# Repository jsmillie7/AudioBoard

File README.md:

# AudioBoard
A repository for a Teensy 4.0 NRF24L01 Audio Transmitter and Receiver board with a built-in codec.

This project supports wireless transmission of mono 16-bit 44.1khz audio bewteen two teensy 4.0 modules.

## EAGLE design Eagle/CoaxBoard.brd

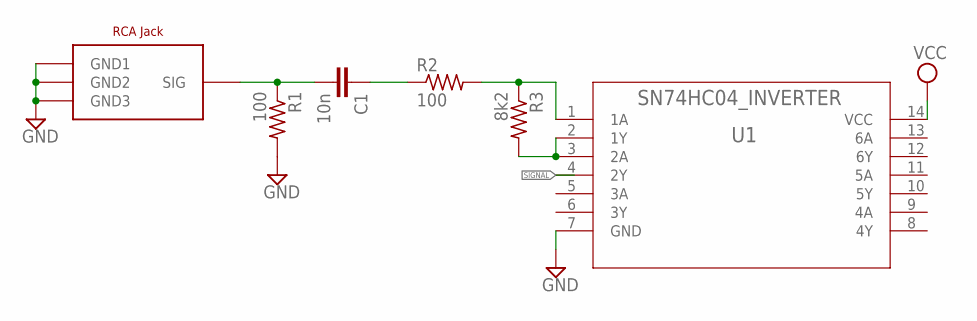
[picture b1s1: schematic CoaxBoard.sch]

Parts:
C1: 10n; C0805
R1, R2: 100; R0805
R3: 8k2; R0805
U1: SN74HC04_INVERTER; NS14
U$1: RCA_JACK

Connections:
GND: R1.2, U1.7 (GND), U$1.GND1, U$1.GND2, U$1.GND3
unnamed: C1.2, R1.1, U$1.SIG
unnamed: C1.1, R2.1
unnamed: R2.2, R3.1, U1.1 (1A)
unnamed: R3.2, U1.2 (1Y), U1.3 (2A)
SIGNAL: U1.4 (2Y)
VCC: U1.14 (VCC)

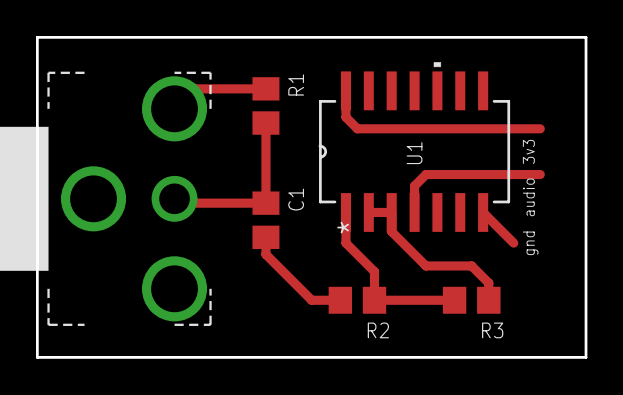
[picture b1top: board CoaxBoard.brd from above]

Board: 2 copper layers, 30.5 x 17.8 mm, 6 parts (0 on the bottom side), 5 nets.

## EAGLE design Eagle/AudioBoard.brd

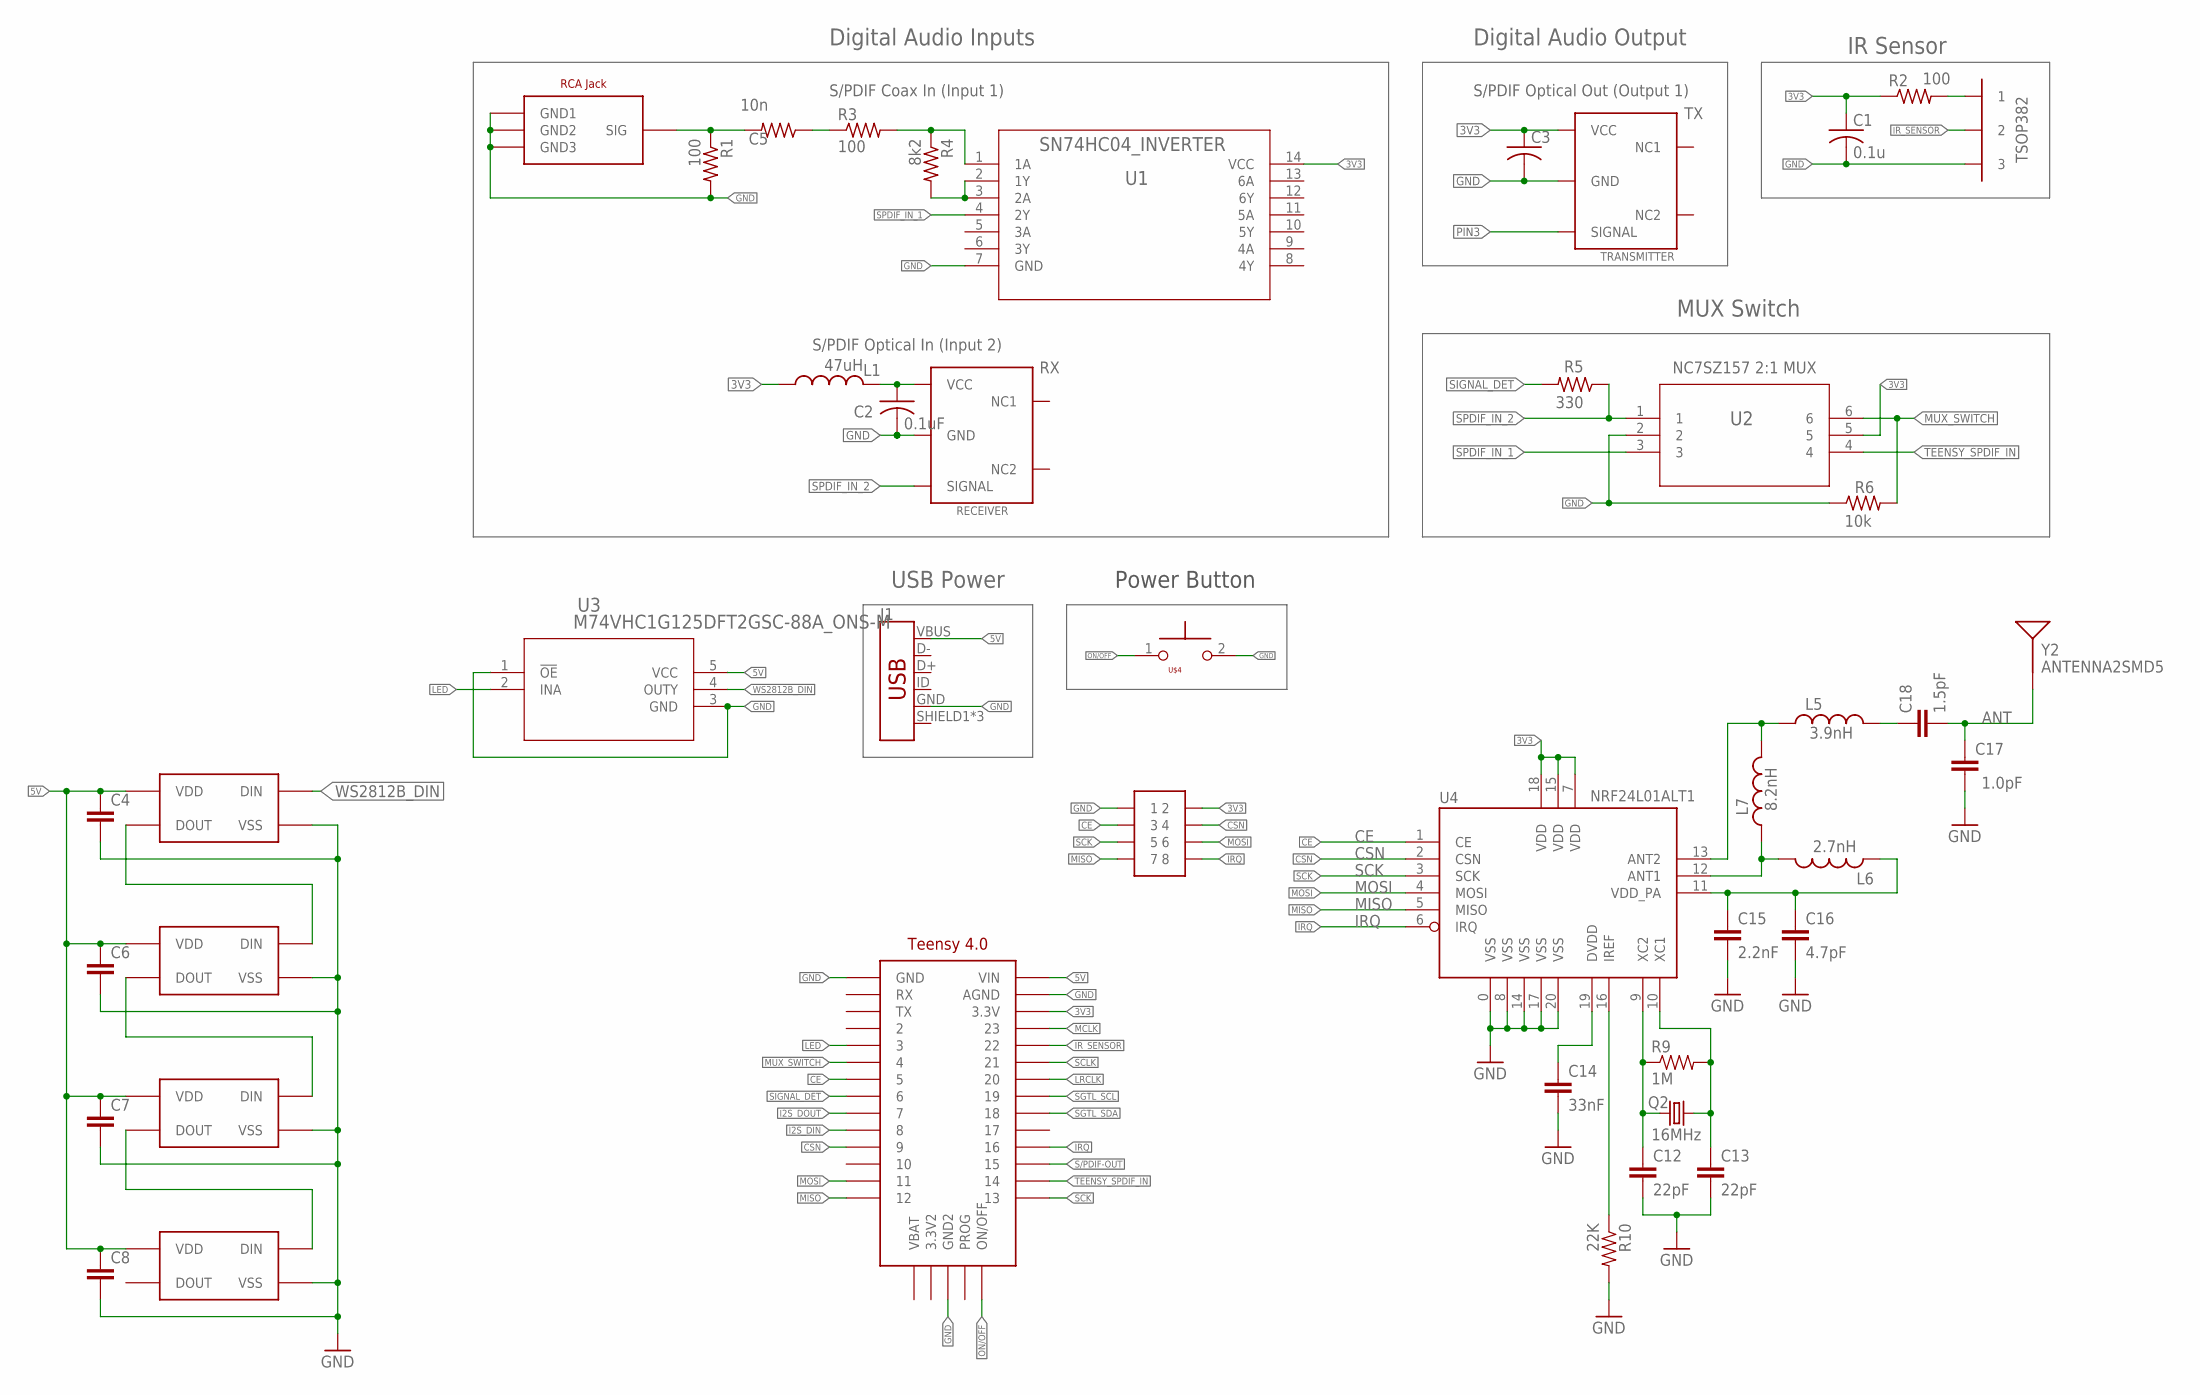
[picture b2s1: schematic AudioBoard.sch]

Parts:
C1: 0.1u; C0603K
C2: 0.1uF; C0603
C3: C-USC0603; C0603
C4, C6, C7, C8: C-EUC0603; C0603
C5: 10n; R0603
C12, C13: 22pF; 0402-CAP
C14: 33nF; 0402-CAP
C15: 2.2nF; 0402-CAP
C16: 4.7pF; 0402-CAP
C17: 1.0pF; 0402-CAP
C18: 1.5pF; 0402-CAP
J1: USB_MICRO-BREDUCED_PASTE; USB-B-MICRO-SMD_RED_PASTE
L1: 47uH; L2012C
L5: 3.9nH; C0402
L6: 2.7nH; C0402
L7: 8.2nH; C0402
Q2: 16MHz; CRYSTAL-SMD-5X3
R1, R2, R3: 100; R0603
R4: 8k2; R0603
R5: 330; R0603
R6: 10k; R0603
R9: 1M; 0402-RES
R10: 22K; 0402-RES
RECEIVER: S/PDIF-IN; SPDIF-IN
TRANSMITTER: S/PDIF-OUT; SPDIF-OUT
U1: SN74HC04_INVERTER; NS14
U2: 2:1_MUX_NC7SZ157P6X; SOIC_Z157P6X_ONS
U3: M74VHC1G125DFT2GSC-88A_ONS-M; SC-88A_ONS-M
U4: NRF24L01ALT1; QFN20_ALT1
U$1: 1X3HEADER
U$2: RCA_JACK
U$3: TEENSY4.0
U$4: SMD_BUTTON; SMD
U$5, U$6, U$7, U$8: WS2812B
U$9: 2X4HEADER
Y2: ANTENNA2SMD5; ANTENNA-CHIP5

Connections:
1TO2: U$5.DOUT, U$6.DIN
2TO3: U$6.DOUT, U$7.DIN
3TO4: U$7.DOUT, U$8.DIN
3V3: C1.1, C3.1, L1.1, R2.1, TRANSMITTER.VCC, U1.14 (VCC), U2.5, U4.7 (VDD), U4.15 (VDD), U4.18 (VDD), U$3.3.3V, U$9.2
5V: C4.1, C6.1, C7.1, C8.1, J1.VBUS, U3.5 (VCC), U$3.VIN, U$5.VDD, U$6.VDD, U$7.VDD, U$8.VDD
ANT: C17.2, C18.2, Y2.FEED
CE: U4.1 (CE), U$3.5, U$9.3
CSN: U4.2 (CSN), U$3.9, U$9.4
GND: C1.2, C2.2, C3.2, C4.2, C6.2, C7.2, C8.2, C12.2, C13.2, C14.2, C15.2, C16.2, C17.1, J1.GND, R1.2, R6.1, R10.2, RECEIVER.GND, TRANSMITTER.GND, U1.7 (GND), U2.2, U3.1 (!OE), U3.3 (GND), U4.0 (VSS), U4.8 (VSS), U4.14 (VSS), U4.17 (VSS), U4.20 (VSS), U$1.P$3 (3), U$2.GND1, U$2.GND2, U$2.GND3, U$3.AGND, U$3.GND, U$3.GND2, U$4.2, U$5.VSS, U$6.VSS, U$7.VSS, U$8.VSS, U$9.1
I2S_DIN: U$3.8
I2S_DOUT: U$3.7
IRQ: U4.6 (IRQ), U$3.16, U$9.8
IR_SENSOR: U$1.P$2 (2), U$3.22
LED: U3.2 (INA), U$3.3
LRCLK: U$3.20
MCLK: U$3.23
MISO: U4.5 (MISO), U$3.12, U$9.7
MOSI: U4.4 (MOSI), U$3.11, U$9.6
MUX_SWITCH: R6.2, U2.6, U$3.4
unnamed: C5.2, R1.1, U$2.SIG
unnamed: R2.2, U$1.P$1 (1)
unnamed: C5.1, R3.1
unnamed: R3.2, R4.1, U1.1 (1A)
unnamed: C2.1, L1.2, RECEIVER.VCC
unnamed: R4.2, U1.2 (1Y), U1.3 (2A)
unnamed: C12.1, Q2.1, R9.1, U4.9 (XC2)
unnamed: C13.1, Q2.3 (2), R9.2, U4.10 (XC1)
unnamed: L5.1, L7.2, U4.13 (ANT2)
unnamed: C15.1, C16.1, L6.1, U4.11 (VDD_PA)
unnamed: R10.1, U4.16 (IREF)
unnamed: C14.1, U4.19 (DVDD)
unnamed: L6.2, L7.1, U4.12 (ANT1)
unnamed: C18.1, L5.2
ON/OFF: U$3.ON/OFF, U$4.1
PIN3: TRANSMITTER.SIGNAL
S/PDIF-OUT: U$3.15
SCK: U4.3 (SCK), U$3.13, U$9.5
SCLK: U$3.21
SGTL_SCL: U$3.19
SGTL_SDA: U$3.18
SIGNAL_DET: R5.2, U$3.6
SPDIF_IN_1: U1.4 (2Y), U2.3
SPDIF_IN_2: R5.1, RECEIVER.SIGNAL, U2.1
TEENSY_SPDIF_IN: U2.4, U$3.14
WS2812B_DIN: U3.4 (OUTY), U$5.DIN

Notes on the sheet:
Power Button
IR Sensor
NC7SZ157 2:1 MUX
S/PDIF Optical In (Input 2)
S/PDIF Coax In (Input 1)
Digital Audio Inputs
Digital Audio Output
MUX Switch
S/PDIF Optical Out (Output 1)
TSOP382
USB Power

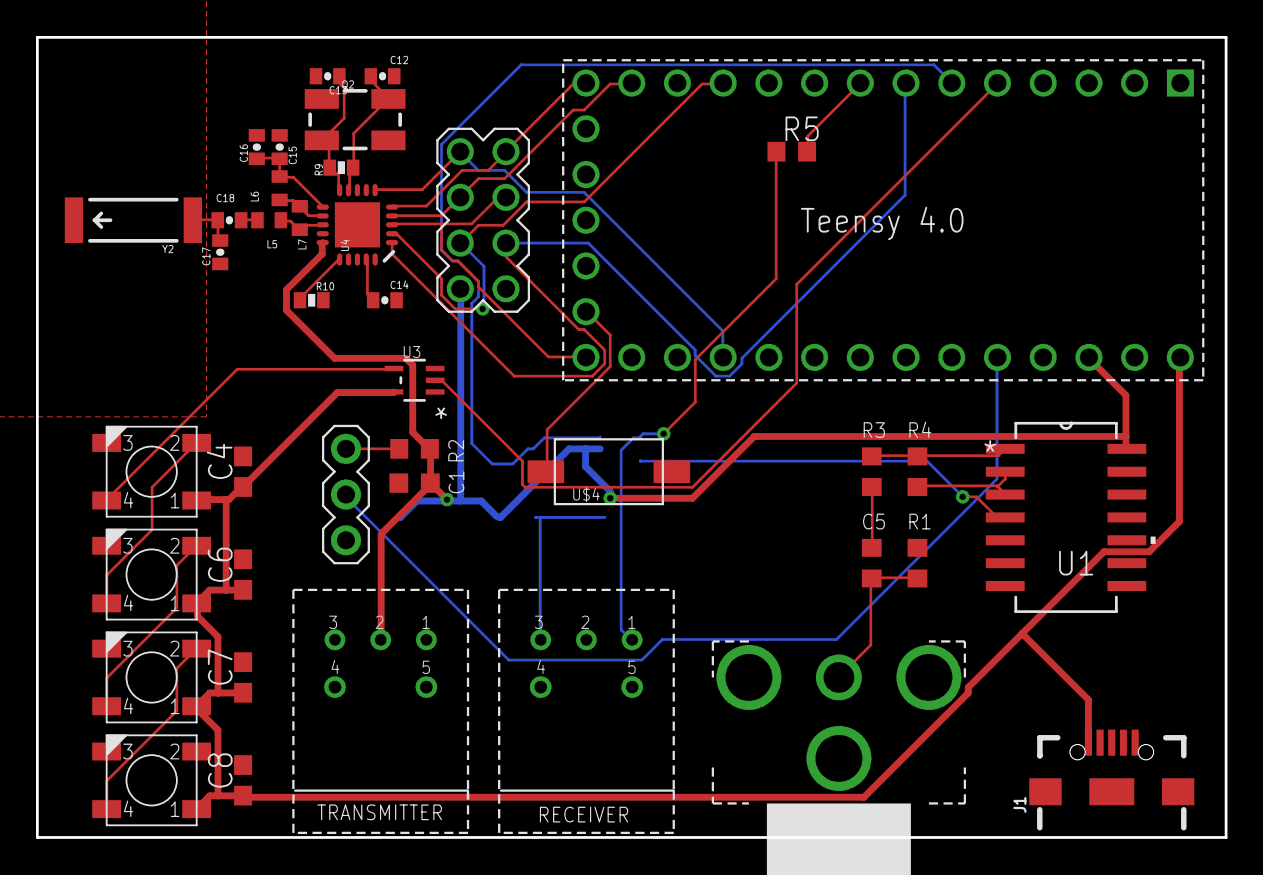
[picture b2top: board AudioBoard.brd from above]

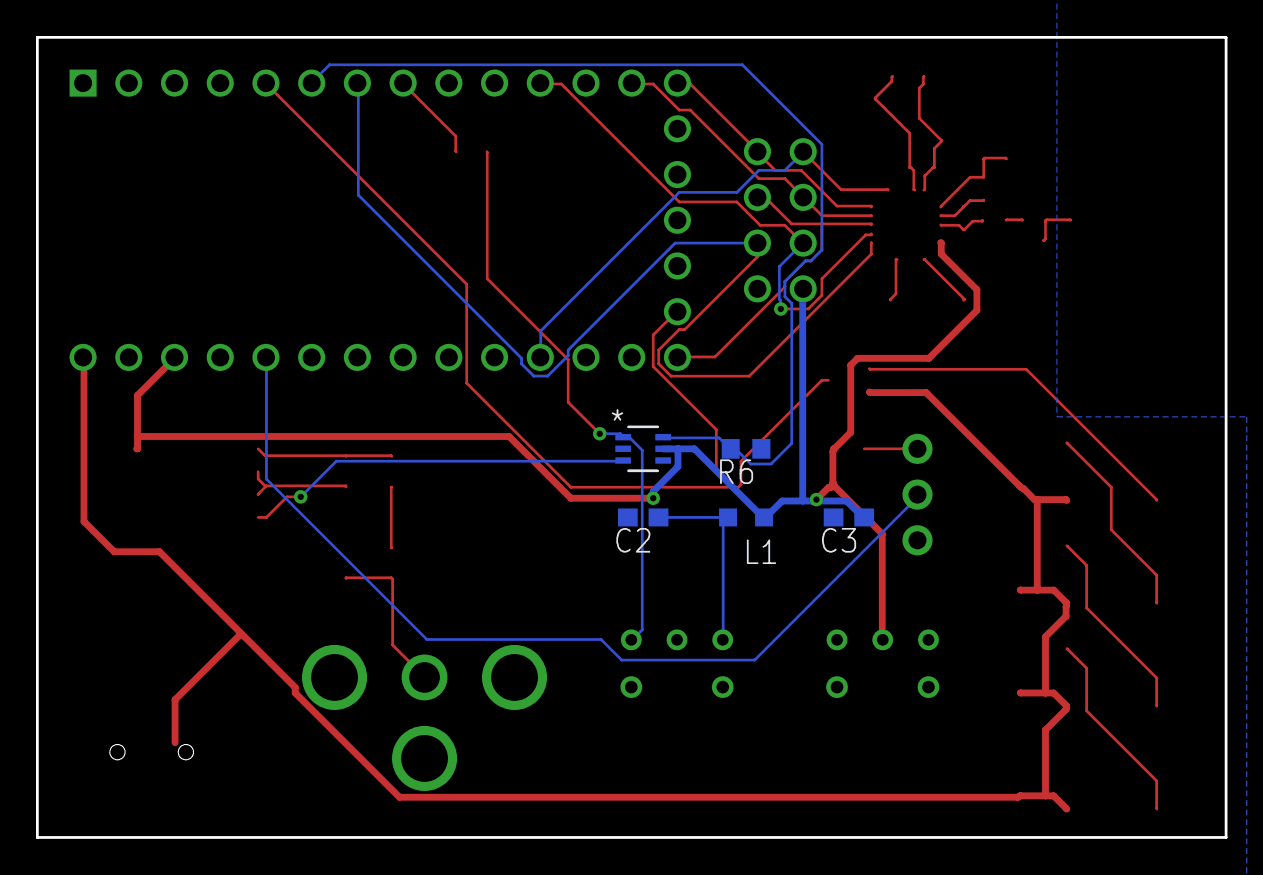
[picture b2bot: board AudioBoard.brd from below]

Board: 2 copper layers, 66.0 x 44.5 mm, 45 parts (5 on the bottom side), 36 nets.

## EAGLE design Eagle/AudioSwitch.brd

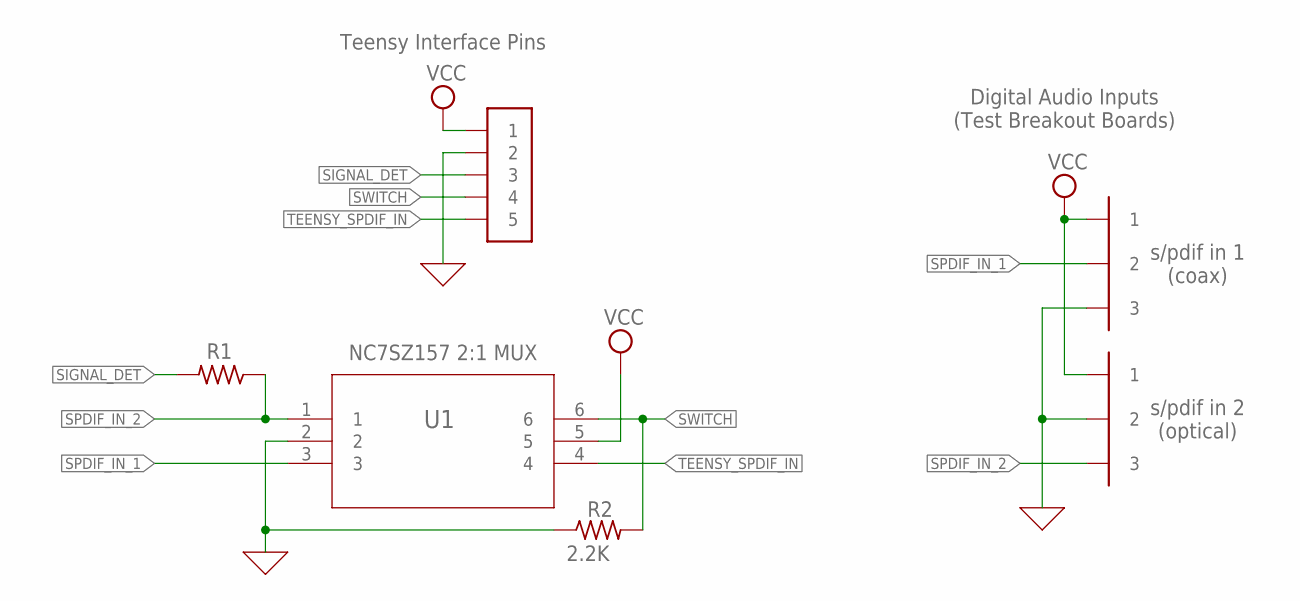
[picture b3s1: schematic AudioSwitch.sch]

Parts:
R1: R-US_R0603; R0603
R2: 2.2K; R0603
U1: 2:1_MUX_NC7SZ157P6X; SOIC_Z157P6X_ONS
U$1: 1X5HEADER
U$2, U$3: 1X3HEADER

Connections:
0: R2.1, U1.2, U$1.P$2 (2), U$2.P$3 (3), U$3.P$2 (2)
SIGNAL_DET: R1.2, U$1.P$3 (3)
SPDIF_IN_1: U1.3, U$2.P$2 (2)
SPDIF_IN_2: R1.1, U1.1, U$3.P$3 (3)
SWITCH: R2.2, U1.6, U$1.P$4 (4)
TEENSY_SPDIF_IN: U1.4, U$1.P$5 (5)
VCC: U1.5, U$1.P$1 (1), U$2.P$1 (1), U$3.P$1 (1)

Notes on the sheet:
s/pdif in 1 (coax)
s/pdif in 2 (optical)
Digital Audio Inputs (Test Breakout Boards)
Teensy Interface Pins
NC7SZ157 2:1 MUX

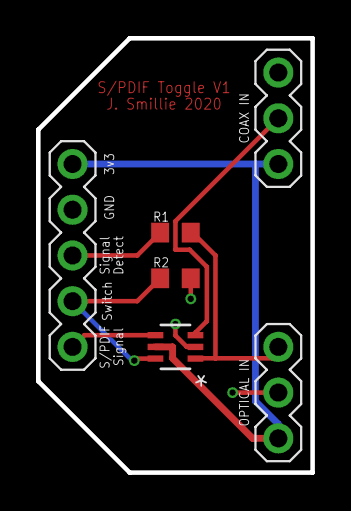
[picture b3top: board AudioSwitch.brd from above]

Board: 2 copper layers, 15.2 x 24.1 mm, 6 parts (0 on the bottom side), 7 nets.

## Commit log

2020-06-28 Eagle File Updates
2020-06-28 adding arduino files
2020-06-28 Working on schematics
2020-06-28 Add BRD file.
2020-06-28 Arduino updates
2020-06-28 schematic and board file work.
2020-07-01 Add Coax test board
2020-07-01 Adding copy of eagle library
2020-07-08 design ordered from Oshpark
2020-07-09 Audio Switch Circuit Files
2020-07-15 update audioboard files
2020-09-18 updates to eagle files
2020-09-18 adding arduino code for the transmitter
2020-09-18 adding infrastructure for IR Receiver

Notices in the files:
parts and their libraries:
SparkFun-Connectors: Licensing: Creative Commons ShareAlike 4.0 International - https://creativecommons.org/licenses/by-sa/4.0
COPYRIGHT: Copyright (C) 2016 Accelerated Designs. All rights reserved
